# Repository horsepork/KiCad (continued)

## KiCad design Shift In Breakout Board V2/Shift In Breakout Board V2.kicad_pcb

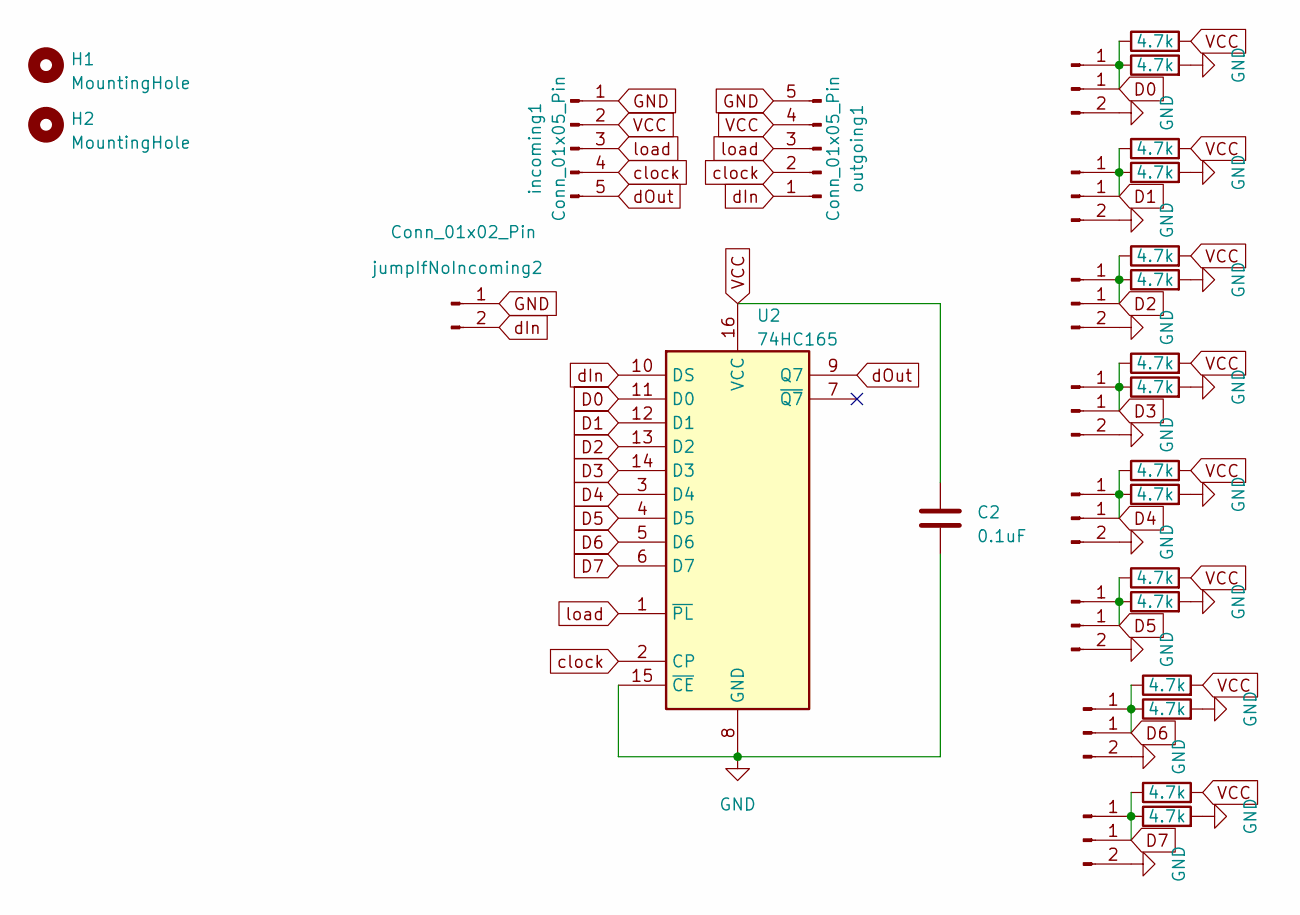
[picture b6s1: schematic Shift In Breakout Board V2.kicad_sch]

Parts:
C2: 0.1uF; C_0805_2012Metric_Pad1.18x1.45mm_HandSolder
D8, D9, D10, D11, D12, D13, D14, D15: Conn_01x02_Pin; Molex_KK-254_AE-6410-02A_1x02_P2.54mm_Vertical
H1, H2: MountingHole; MountingHole_3.2mm_M3
J1, J2, J3, J4, J5, J6, J7, J8: Conn_01x01_Pin; PinHeader_1x01_P2.54mm_Vertical
R1, R2, R3, R4, R5, R6, R7, R8, R9, R10, R11, R12, R13, R14, R15, R16: 4.7k; R_0805_2012Metric_Pad1.20x1.40mm_HandSolder
U2: 74HC165; SOIC-16_3.9x9.9mm_P1.27mm
incoming1: Conn_01x05_Pin; Molex_KK-254_AE-6410-05A_1x05_P2.54mm_Vertical
jumpIfNoIncoming2: Conn_01x02_Pin; SolderJumper-2_P1.3mm_Open_RoundedPad1.0x1.5mm
outgoing1: Conn_01x05_Pin; Molex_KK-254_AE-6410-05A_1x05_P2.54mm_Vertical

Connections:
D0: D8.1, J1.1, R1.1, R2.1, U2.11 (D0)
D1: D9.1, J2.1, R3.1, R4.1, U2.12 (D1)
D2: D10.1, J3.1, R5.1, R6.1, U2.13 (D2)
D3: D11.1, J4.1, R7.1, R8.1, U2.14 (D3)
D4: D12.1, J5.1, R9.1, R10.1, U2.3 (D4)
D5: D13.1, J6.1, R11.1, R12.1, U2.4 (D5)
D6: D14.1, J7.1, R13.1, R14.1, U2.5 (D6)
D7: D15.1, J8.1, R15.1, R16.1, U2.6 (D7)
GND: C2.2, D8.2, D9.2, D10.2, D11.2, D12.2, D13.2, D14.2, D15.2, R2.2, R4.2, R6.2, R8.2, R10.2, R12.2, R14.2, R16.2, U2.8 (GND), U2.15 (~CE), incoming1.1, jumpIfNoIncoming2.1, outgoing1.5
VCC: C2.1, R1.2, R3.2, R5.2, R7.2, R9.2, R11.2, R13.2, R15.2, U2.16 (VCC), incoming1.2, outgoing1.4
clock: U2.2 (CP), incoming1.4, outgoing1.2
dIn: U2.10 (DS), jumpIfNoIncoming2.2, outgoing1.1
dOut: U2.9 (Q7), incoming1.5
load: U2.1 (~PL), incoming1.3, outgoing1.3

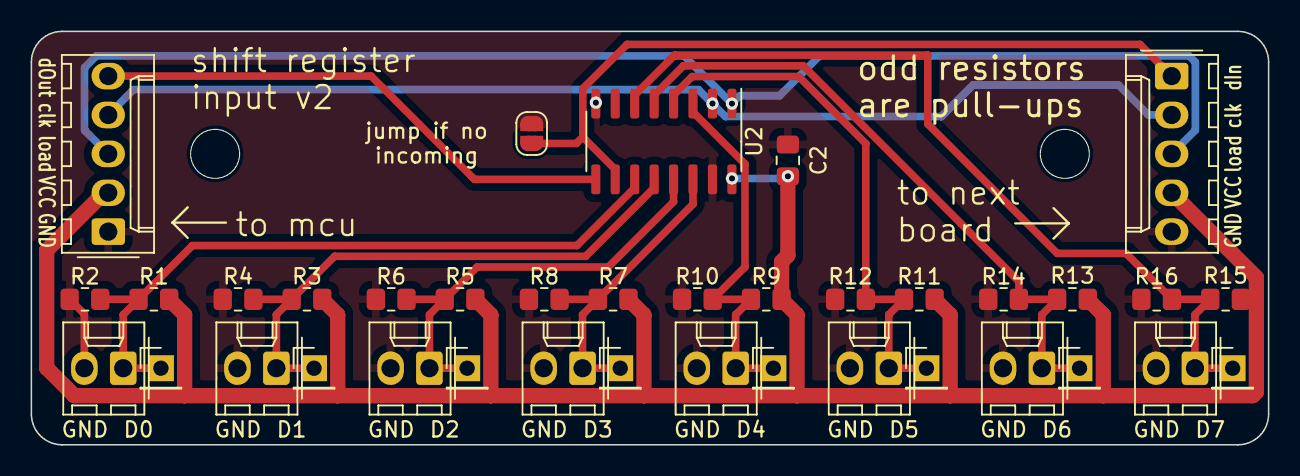
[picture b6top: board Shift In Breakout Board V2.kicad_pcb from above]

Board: 2 copper layers, 80.8 x 27.0 mm, 39 parts (0 on the bottom side), 14 nets.

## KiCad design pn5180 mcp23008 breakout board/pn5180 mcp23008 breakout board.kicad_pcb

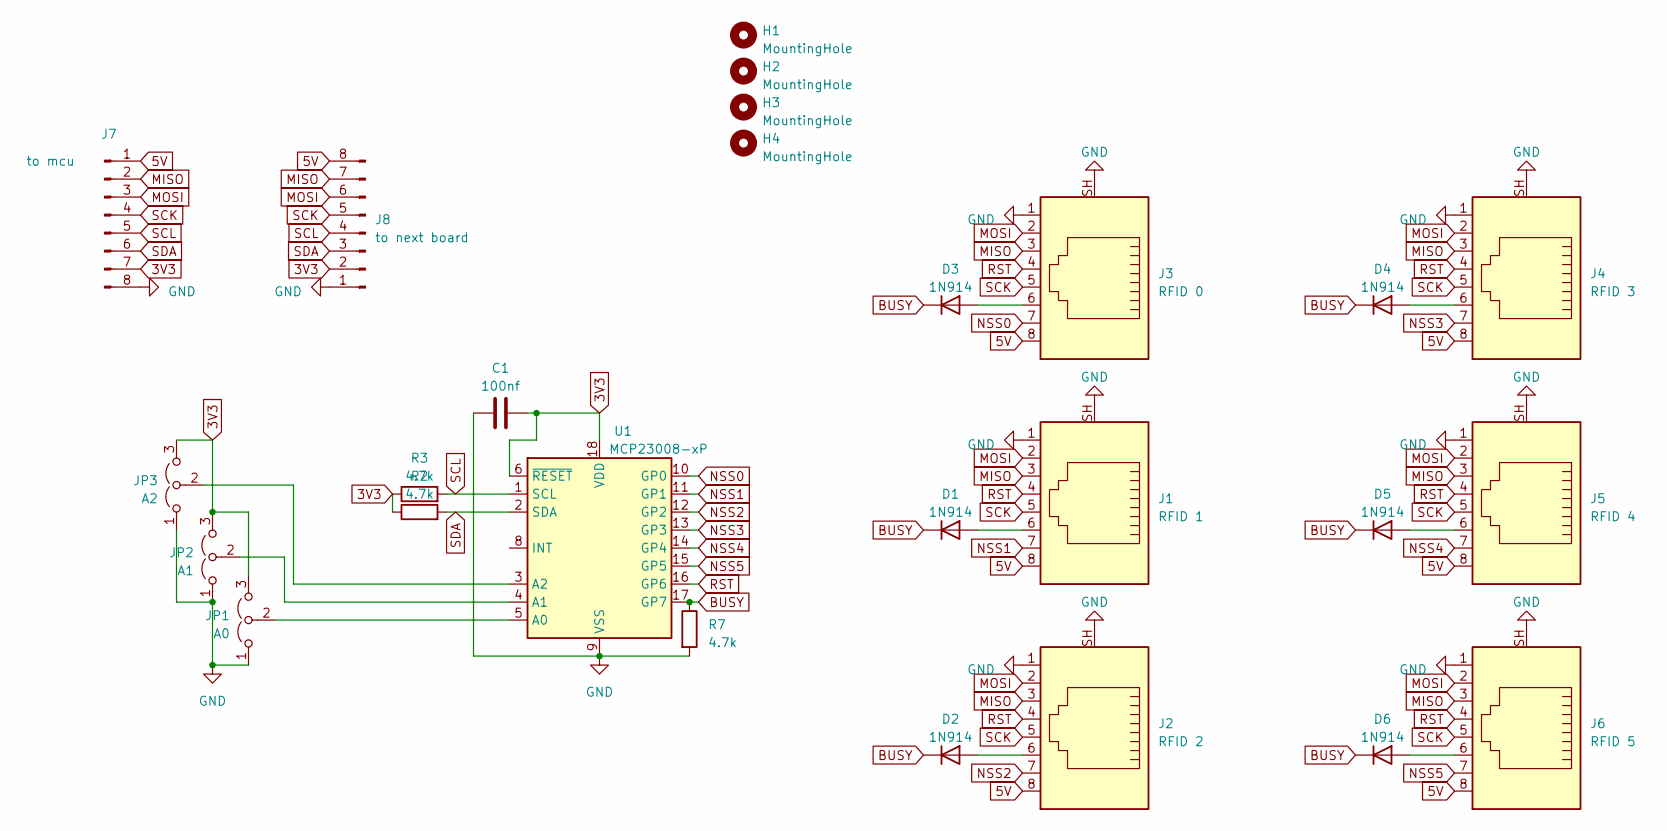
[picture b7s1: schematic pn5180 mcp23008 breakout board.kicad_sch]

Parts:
C1: 100nf; C_Disc_D6.0mm_W2.5mm_P5.00mm
D1, D2, D3, D4, D5, D6: 1N914; D_DO-35_SOD27_P7.62mm_Horizontal
H1, H2, H3, H4: MountingHole; MountingHole_3.2mm_M3
J1: RFID 1; RJ45_Ninigi_GE
J2: RFID 2; RJ45_Ninigi_GE
J3: RFID 0; RJ45_Ninigi_GE
J4: RFID 3; RJ45_Ninigi_GE
J5: RFID 4; RJ45_Ninigi_GE
J6: RFID 5; RJ45_Ninigi_GE
J7: to mcu; Molex_KK-254_AE-6410-08A_1x08_P2.54mm_Vertical
J8: to next board; Molex_KK-254_AE-6410-08A_1x08_P2.54mm_Vertical
JP1: A0; SolderJumper-3_P1.3mm_Open_RoundedPad1.0x1.5mm
JP2: A1; SolderJumper-3_P1.3mm_Open_RoundedPad1.0x1.5mm
JP3: A2; SolderJumper-3_P1.3mm_Open_RoundedPad1.0x1.5mm
R2, R3, R7: 4.7k; R_Axial_DIN0207_L6.3mm_D2.5mm_P7.62mm_Horizontal
U1: MCP23008-xP; DIP-18_W7.62mm

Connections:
3V3: C1.2, J7.7, J8.2, JP1.3 (B), JP2.3 (B), JP3.3 (B), R2.1, R3.1, U1.6 (~RESET), U1.18 (VDD)
5V: J1.8, J2.8, J3.8, J4.8, J5.8, J6.8, J7.1, J8.8
BUSY: D1.1 (K), D2.1 (K), D3.1 (K), D4.1 (K), D5.1 (K), D6.1 (K), R7.1, U1.17 (GP7)
GND: C1.1, J1.1, J1.SH, J2.1, J2.SH, J3.1, J3.SH, J4.1, J4.SH, J5.1, J5.SH, J6.1, J6.SH, J7.8, J8.1, JP1.1 (A), JP2.1 (A), JP3.1 (A), R7.2, U1.9 (VSS)
MISO: J1.3, J2.3, J3.3, J4.3, J5.3, J6.3, J7.2, J8.7
MOSI: J1.2, J2.2, J3.2, J4.2, J5.2, J6.2, J7.3, J8.6
NSS0: J3.7, U1.10 (GP0)
NSS1: J1.7, U1.11 (GP1)
NSS2: J2.7, U1.12 (GP2)
NSS3: J4.7, U1.13 (GP3)
NSS4: J5.7, U1.14 (GP4)
NSS5: J6.7, U1.15 (GP5)
unnamed: D1.2 (A), J1.6
unnamed: D2.2 (A), J2.6
unnamed: D3.2 (A), J3.6
unnamed: D4.2 (A), J4.6
unnamed: D5.2 (A), J5.6
unnamed: D6.2 (A), J6.6
unnamed: JP1.2 (C), U1.5 (A0)
unnamed: JP2.2 (C), U1.4 (A1)
unnamed: JP3.2 (C), U1.3 (A2)
RST: J1.4, J2.4, J3.4, J4.4, J5.4, J6.4, U1.16 (GP6)
SCK: J1.5, J2.5, J3.5, J4.5, J5.5, J6.5, J7.4, J8.5
SCL: J7.5, J8.4, R3.2, U1.1 (SCL)
SDA: J7.6, J8.3, R2.2, U1.2 (SDA)

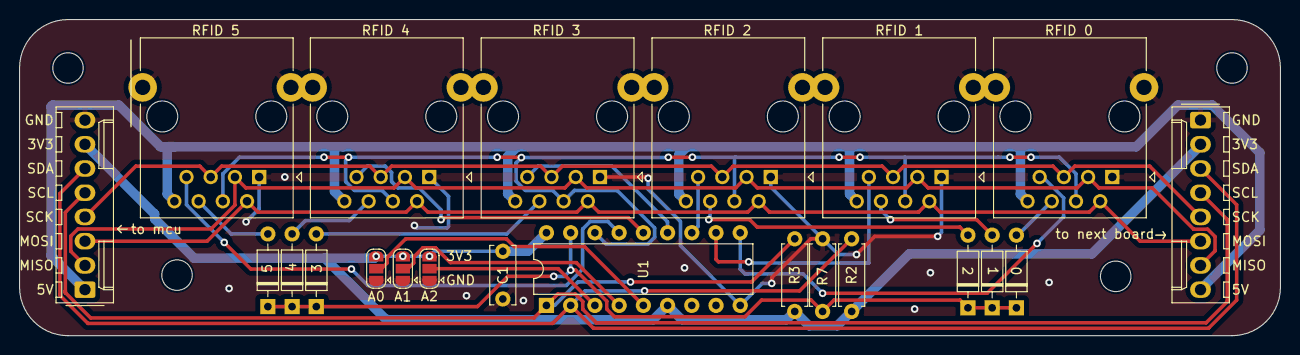
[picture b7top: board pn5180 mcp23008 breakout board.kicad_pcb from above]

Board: 2 copper layers, 132.2 x 33.1 mm, 26 parts (0 on the bottom side), 25 nets.

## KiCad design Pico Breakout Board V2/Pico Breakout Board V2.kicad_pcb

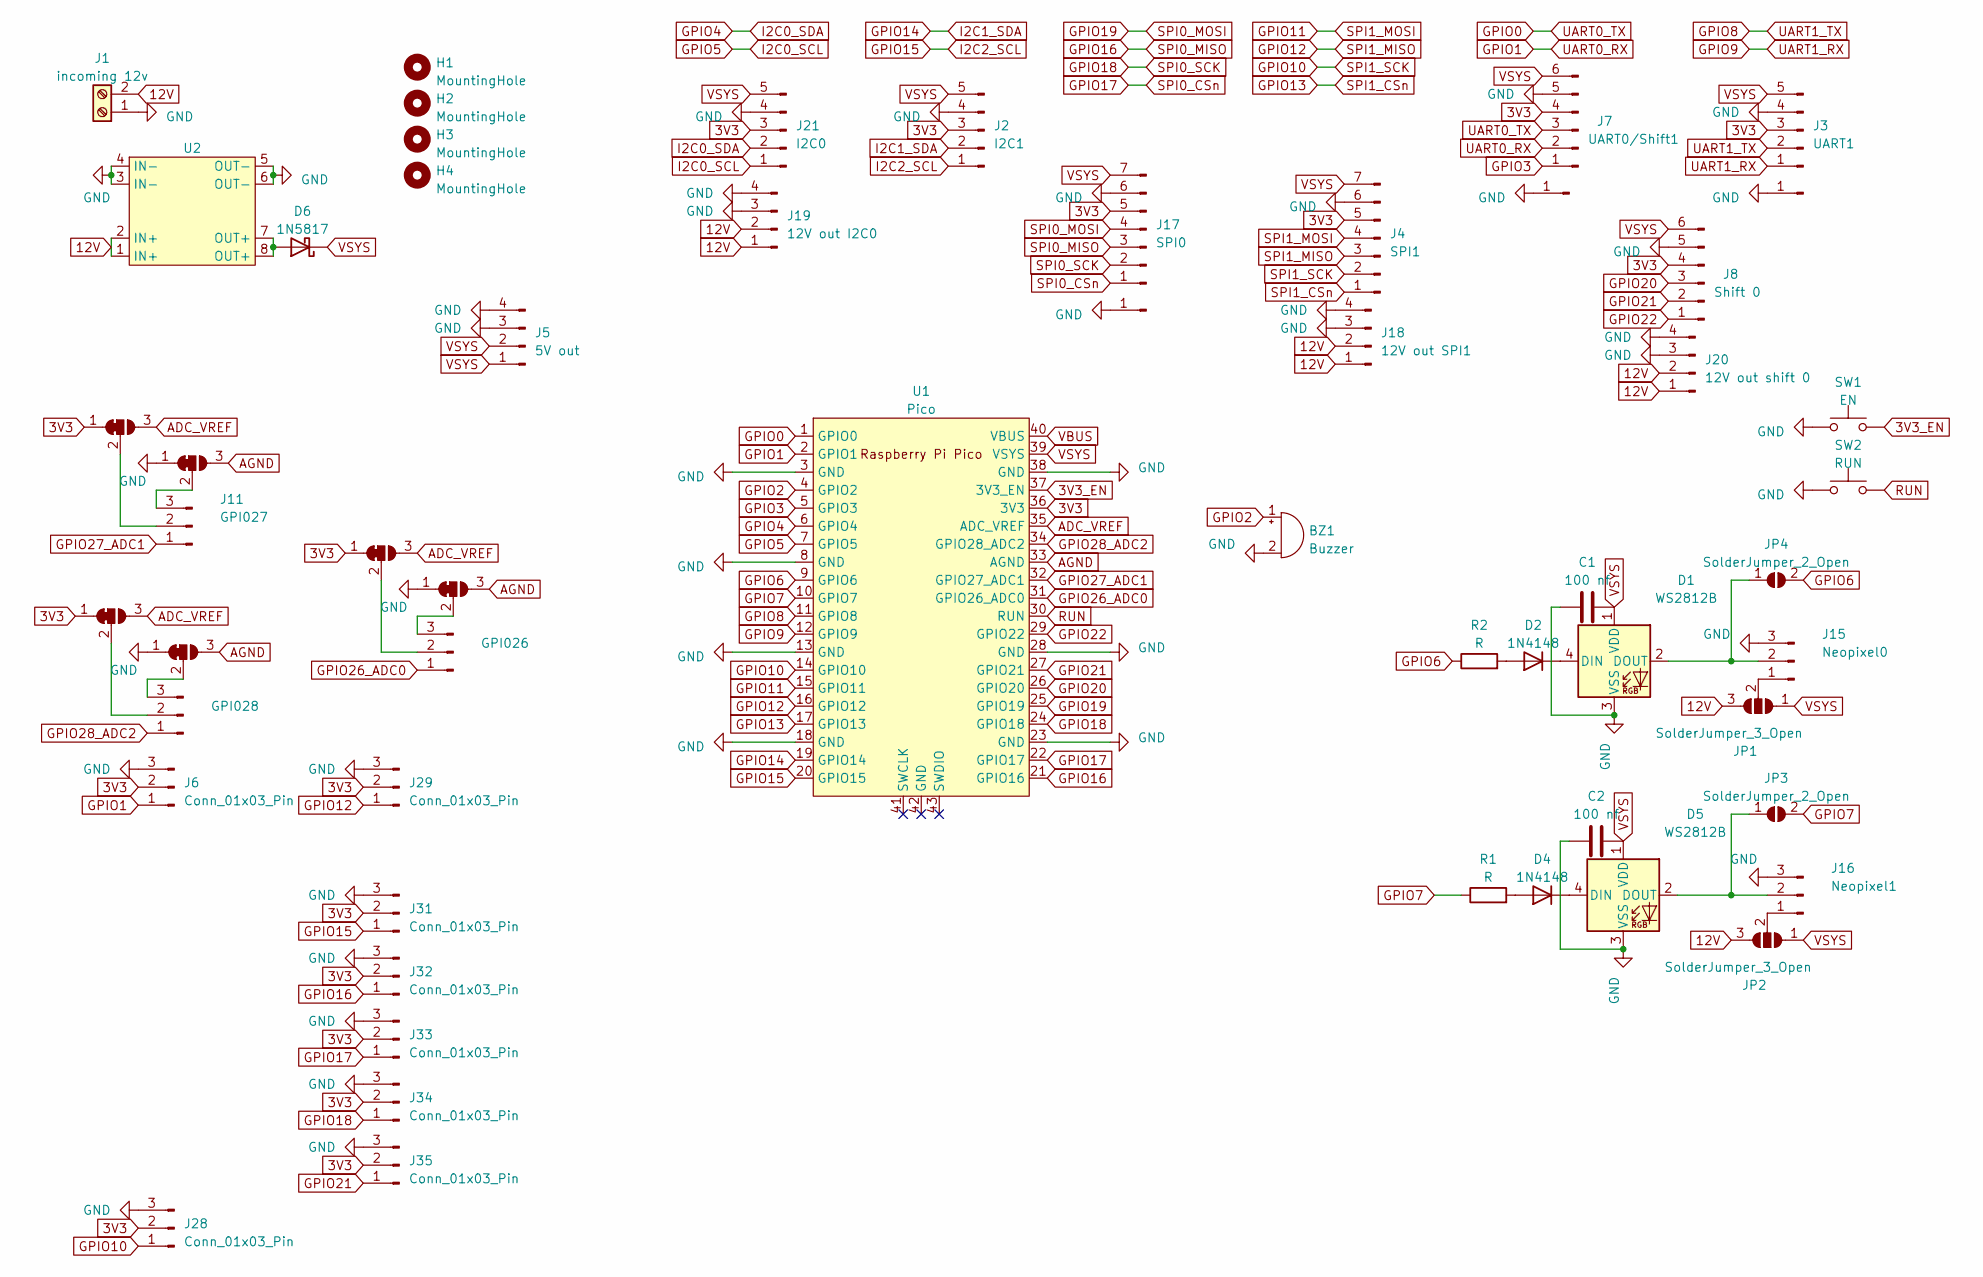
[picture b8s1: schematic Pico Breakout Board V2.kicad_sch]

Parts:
BZ1: Buzzer; Buzzer_12x9.5RM7.6
C1, C2: 100 nf; C_Disc_D8.0mm_W2.5mm_P5.00mm
D1, D5: WS2812B; LED_WS2812B_PLCC4_5.0x5.0mm_P3.2mm
D2, D4: 1N4148; D_DO-35_SOD27_P7.62mm_Horizontal
D6: 1N5817; D_DO-41_SOD81_P10.16mm_Horizontal
H1, H2, H3, H4: MountingHole; MountingHole_3.2mm_M3
J1: incoming 12v; TerminalBlock_bornier-2_P5.08mm
J2: I2C1; Molex_KK-254_AE-6410-05A_1x05_P2.54mm_Vertical
J3: UART1; Molex_KK-254_AE-6410-05A_1x05_P2.54mm_Vertical
J4: SPI1; Molex_KK-254_AE-6410-07A_1x07_P2.54mm_Vertical
J5: 5V out; Molex_KK-254_AE-6410-04A_1x04_P2.54mm_Vertical
J6, J28, J29, J31, J32, J33, J34, J35: Conn_01x03_Pin; Molex_KK-254_AE-6410-03A_1x03_P2.54mm_Vertical
J7: UART0/Shift1; Molex_KK-254_AE-6410-06A_1x06_P2.54mm_Vertical
J8: Shift 0; Molex_KK-254_AE-6410-06A_1x06_P2.54mm_Vertical
J9: GPI026; Molex_KK-254_AE-6410-03A_1x03_P2.54mm_Vertical
J10, J12, J14: Conn_01x01_Pin; PinHeader_1x01_P2.54mm_Vertical
J11: GPI027; Molex_KK-254_AE-6410-03A_1x03_P2.54mm_Vertical
J13: GPI028; Molex_KK-254_AE-6410-03A_1x03_P2.54mm_Vertical
J15: Neopixel0; Molex_KK-254_AE-6410-03A_1x03_P2.54mm_Vertical
J16: Neopixel1; Molex_KK-254_AE-6410-03A_1x03_P2.54mm_Vertical
J17: SPI0; Molex_KK-254_AE-6410-07A_1x07_P2.54mm_Vertical
J18: 12V out SPI1; Molex_KK-254_AE-6410-04A_1x04_P2.54mm_Vertical
J19: 12V out I2C0; Molex_KK-254_AE-6410-04A_1x04_P2.54mm_Vertical
J20: 12V out shift 0; Molex_KK-254_AE-6410-04A_1x04_P2.54mm_Vertical
J21: I2C0; Molex_KK-254_AE-6410-05A_1x05_P2.54mm_Vertical
JP1, JP2: SolderJumper_3_Open; 3 pads
JP3, JP4: SolderJumper_2_Open; SolderJumper-2_P1.3mm_Open_RoundedPad1.0x1.5mm
JP5, JP6, JP7, JP8, JP9, JP10: SolderJumper_3_Bridged12; SolderJumper-3_P1.3mm_Bridged12_RoundedPad1.0x1.5mm
R1, R2: R; R_Axial_DIN0204_L3.6mm_D1.6mm_P7.62mm_Horizontal
SW1: EN; SW_SPST_B3U-1000P
SW2: RUN; SW_SPST_B3U-1000P
U1: Pico; RPi_Pico_SMD_TH_No_Pads_No_Debug_No_USB
U2: Mini MP1584EN

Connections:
3V3: J2.3, J3.3, J4.5, J6.2, J7.4, J8.4, J17.5, J21.3, J28.2, J29.2, J31.2, J32.2, J33.2, J34.2, J35.2, JP6.1 (A), JP7.1 (A), JP9.1 (A), U1.36 (3V3)
3V3_EN: SW1.2, U1.37 (3V3_EN)
12V: J1.2, J18.1, J18.2, J19.1, J19.2, J20.1, J20.2, JP1.3 (B), JP2.3 (B), U2.1 (IN+), U2.2 (IN+)
ADC_VREF: JP6.3 (B), JP7.3 (B), JP9.3 (B), U1.35 (ADC_VREF)
AGND: JP5.3 (B), JP8.3 (B), JP10.3 (B), U1.33 (AGND)
GND: BZ1.2 (+), C1.2, C2.2, D1.3 (VSS), D5.3 (VSS), J1.1, J2.4, J3.4, J4.6, J5.3, J5.4, J6.3, J7.5, J8.5, J10.1, J12.1, J14.1, J15.3, J16.3, J17.6, J18.3, J18.4, J19.3, J19.4, J20.3, J20.4, J21.4, J28.3, J29.3, J31.3, J32.3, J33.3, J34.3, J35.3, JP5.1 (A), JP8.1 (A), JP10.1 (A), SW1.1, SW2.1, U1.3 (GND), U1.8 (GND), U1.13 (GND), U1.18 (GND), U1.23 (GND), U1.28 (GND), U1.38 (GND), U2.3 (IN-), U2.4 (IN-), U2.5 (OUT-), U2.6 (OUT-)
GPIO0: J7.3, U1.1 (GPIO0)
GPIO1: J6.1, J7.2, U1.2 (GPIO1)
GPIO2: BZ1.1 (-), U1.4 (GPIO2)
GPIO3: J7.1, U1.5 (GPIO3)
GPIO4: J21.2, U1.6 (GPIO4)
GPIO5: J21.1, U1.7 (GPIO5)
GPIO6: JP4.2 (B), R2.1, U1.9 (GPIO6)
GPIO7: JP3.2 (B), R1.1, U1.10 (GPIO7)
GPIO8: J3.2, U1.11 (GPIO8)
GPIO9: J3.1, U1.12 (GPIO9)
GPIO10: J4.2, J28.1, U1.14 (GPIO10)
GPIO11: J4.4, U1.15 (GPIO11)
GPIO12: J4.3, J29.1, U1.16 (GPIO12)
GPIO13: J4.1, U1.17 (GPIO13)
GPIO14: J2.2, U1.19 (GPIO14)
GPIO15: J2.1, J31.1, U1.20 (GPIO15)
GPIO16: J17.3, J32.1, U1.21 (GPIO16)
GPIO17: J17.1, J33.1, U1.22 (GPIO17)
GPIO18: J17.2, J34.1, U1.24 (GPIO18)
GPIO19: J17.4, U1.25 (GPIO19)
GPIO20: J8.3, U1.26 (GPIO20)
GPIO21: J8.2, J35.1, U1.27 (GPIO21)
GPIO22: J8.1, U1.29 (GPIO22)
GPIO26_ADC0: J9.1, U1.31 (GPIO26_ADC0)
GPIO27_ADC1: J11.1, U1.32 (GPIO27_ADC1)
GPIO28_ADC2: J13.1, U1.34 (GPIO28_ADC2)
unnamed: D1.4 (DIN), D2.1 (K)
unnamed: D1.2 (DOUT), J15.2, JP4.1 (A)
unnamed: D2.2 (A), R2.2
unnamed: D4.2 (A), R1.2
unnamed: D4.1 (K), D5.4 (DIN)
unnamed: D5.2 (DOUT), J16.2, JP3.1 (A)
unnamed: D6.2 (A), U2.7 (OUT+), U2.8 (OUT+)
unnamed: J9.2, JP9.2 (C)
unnamed: J9.3, JP10.2 (C)
unnamed: J11.2, JP6.2 (C)
unnamed: J11.3, JP5.2 (C)
unnamed: J13.2, JP7.2 (C)
unnamed: J13.3, JP8.2 (C)
unnamed: J15.1, JP1.2 (C)
unnamed: J16.1, JP2.2 (C)
RUN: SW2.2, U1.30 (RUN)
VBUS: U1.40 (VBUS)
VSYS: C1.1, C2.1, D1.1 (VDD), D5.1 (VDD), D6.1 (K), J2.5, J3.5, J4.7, J5.1, J5.2, J7.6, J8.6, J17.7, J21.5, JP1.1 (A), JP2.1 (A), U1.39 (VSYS)

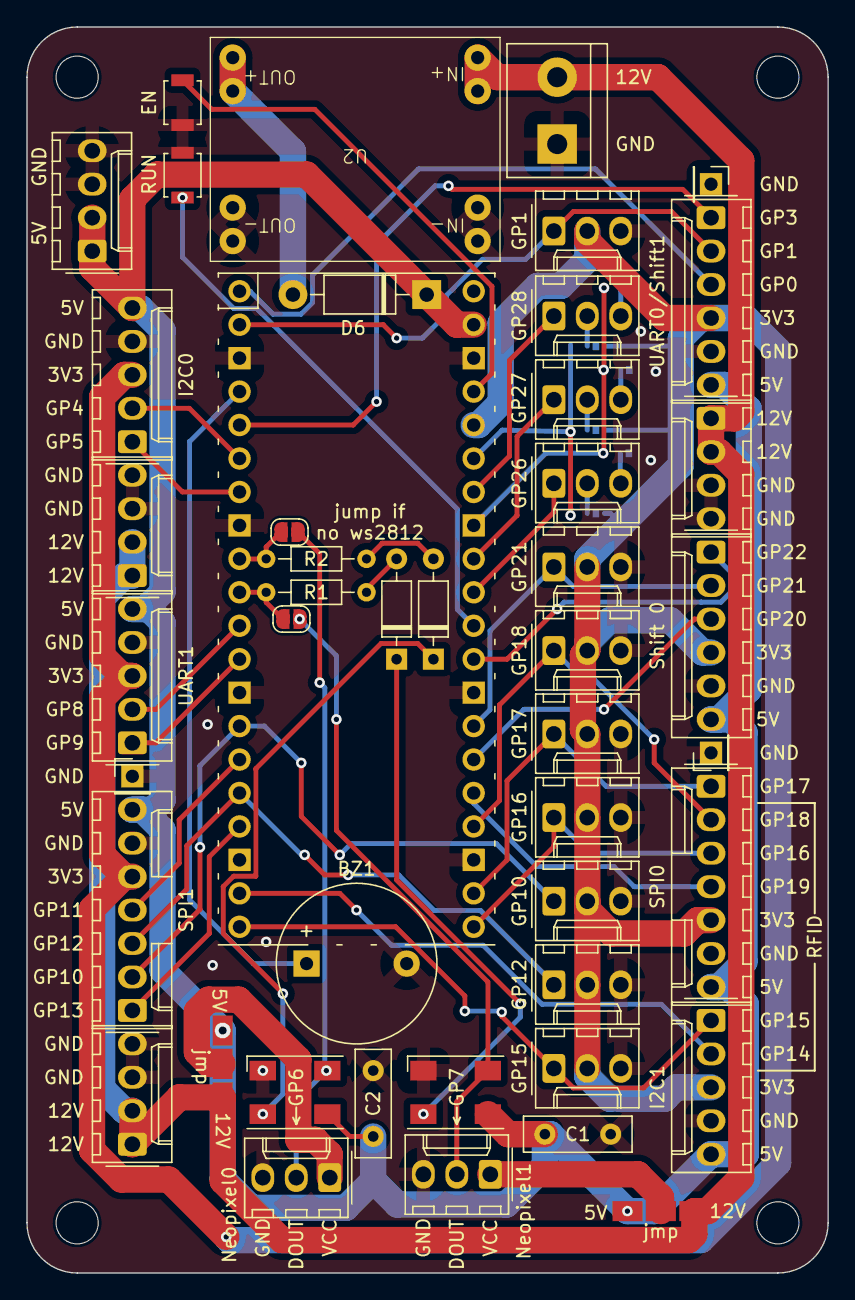
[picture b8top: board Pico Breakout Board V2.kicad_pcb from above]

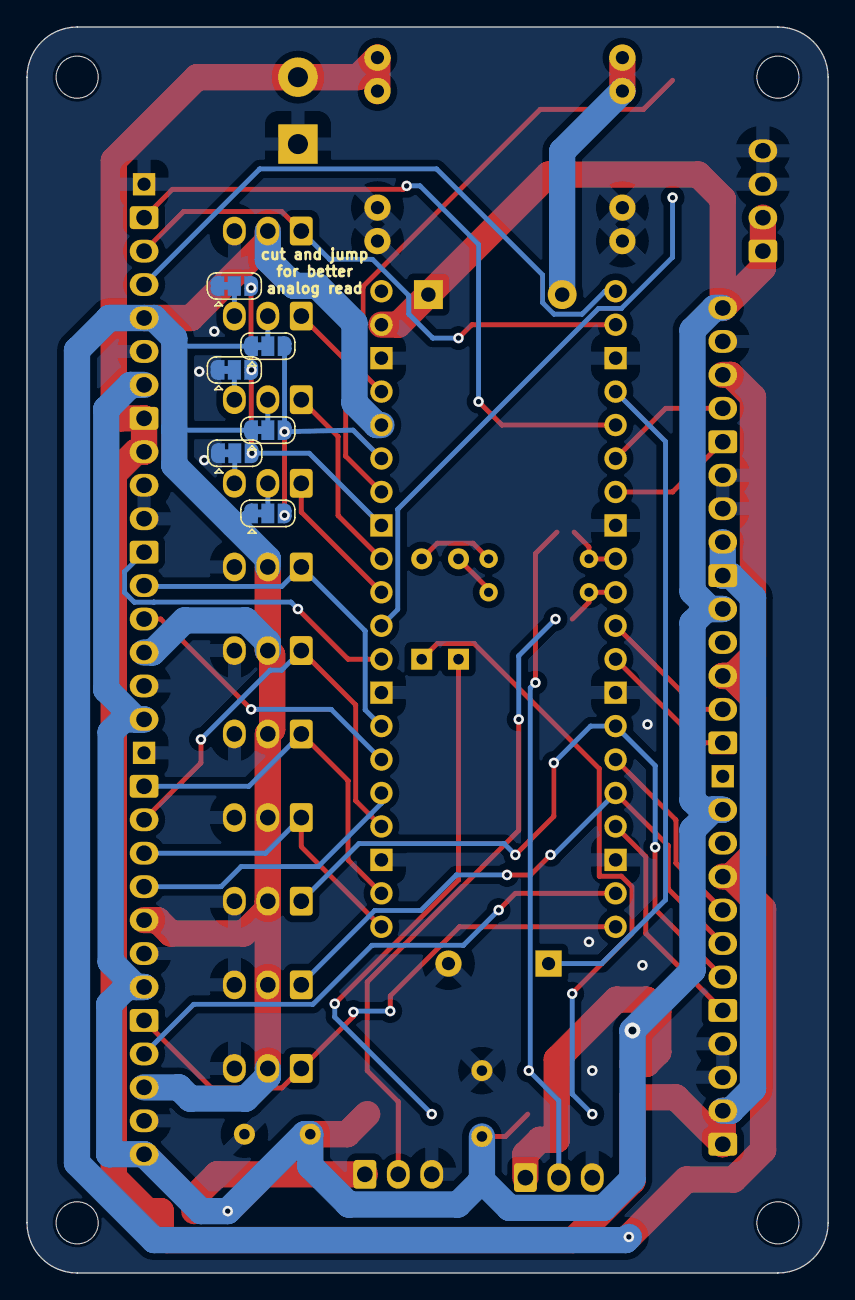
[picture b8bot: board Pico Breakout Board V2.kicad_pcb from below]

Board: 2 copper layers, 60.8 x 94.6 mm, 56 parts (6 on the bottom side), 49 nets.

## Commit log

2023-09-08 added the files
2023-09-15 asdf
2023-12-06 So much
